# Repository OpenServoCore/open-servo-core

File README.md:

<p align="center">
  <picture>
    <source media="(prefers-color-scheme: dark)" srcset="docs/logo-dark.svg">
    
  </picture>
</p>

# OpenServoCore

> An open platform for turning cheap servos into smart actuators.

OpenServoCore (OSC) is open hardware and firmware that drops a CH32V006 control board into a $2-3 cloned hobby servo (SG90 and friends) and turns it into a Dynamixel-class smart actuator with position feedback, current sensing, bus addressing, and programmability. The bus speaks the **osc-native protocol**, a break-framed wire protocol designed to run whole on sub-$0.20 MCUs ([design writeup](https://aaronqian.com/log/2026-08-08-servo-protocol-stream-processing/)).

The thesis is the price point. At mass-production volume, an OSC swap board should add **no more than ~$1 to the BOM** of a cloned servo. That is cheap enough that upgrading every servo in a robot to smart becomes the default instead of a premium decision.

If you are here for a board, jump to [Boards](#boards). The firmware and its progress are in [Firmware](#firmware), and the design writeups are in [Reading](#reading).

## Status

**In active development. Nothing here is shippable yet.** What exists today:

- The **OSC Dev CH32** dev board is validated (Rev B) and you can order one.
- The firmware's protocol and bus transport are implemented and bench-proven on real silicon. Control loops are next.
- **[tinyboot](https://github.com/OpenServoCore/tinyboot)**, the OSC bootloader, has shipped v0.4.0 as its own repo.

The servo swap board (the one that goes inside a servo) is designed but not spun yet.

## Boards

**OSC Dev CH32** (`hardware/boards/osc-dev-v006/`) is the firmware development platform. It accepts any gutted hobby servo, takes power from USB-C, 1S-2S LiPo, or a WCH-LinkE, and fans out every rail and signal to edge test points. Rev B is validated. The [board README](hardware/boards/osc-dev-v006/README.md) has full schematics, pinouts, jumper behaviour, and bringup notes.

Want one? The full KiCad design files live in `hardware/boards/osc-dev-v006/`, ready to send to the board house of your choice.

There is also an experimental BLDC variant (`osc-dev-m007`) in the tree. It is unvalidated, so don't fab it.

## Firmware

The firmware is written in Rust and lives in `firmware/`. It is organized as chip-agnostic library crates (protocol, drivers, control table, discrete-event integration tests), a CH32 chip crate, and board binaries. The chip-agnostic layers compile and unit-test on a desktop with no hardware attached, and a discrete-event simulation runs the production crates ([the architecture writeup](https://aaronqian.com/log/2026-08-01-chip-agnostic-architecture-bare-metal-rust/) covers how).

What works today is the osc-native protocol and the servo bus transport. On the bench that means 0.5-3 Mbaud multi-servo status chains, ~30 µs ping turnaround at 1 Mbaud, and hardware CRC in both directions. The register-table conventions (flat control table, staged writes, alert semantics) will feel familiar if you have used Dynamixel. Control loops, persistence, and safety features are in progress, and build instructions will appear as the firmware matures.

Release and bench images are built with `scripts/build-image.sh <rev>` (add `--bench` for the bench-feature app, `--window` for the bench app with the window record). It exports the commit to one fixed directory (`$OSC_BUILD_ROOT`, default `~/.cache/osc-build`), builds every board image there and prints each image's sha1. The fixed path matters: cargo hashes the absolute path of each path dependency outside the workspace being built into crate metadata, rustc orders functions by the resulting symbol names, and so one commit built from two checkout paths links two layouts. On the V006 a layout shift moves timing by tens of cycles, so every image that is flashed, priced or compared comes from the script. [V006 performance](docs/v006-performance.md) covers the fetch model, the code-shape guards and how to measure a change.

The bootloader, [tinyboot](https://github.com/OpenServoCore/tinyboot), is a separate repo. It is part of the OSC firmware stack but versioned and released independently, and it supports more chips than the OSC boards on purpose (V003 / V00x / V103).

## Reading

The deep-dive writeups live on the blog:

- **[Stream processing on the wire](https://aaronqian.com/log/2026-08-08-servo-protocol-stream-processing/)**: the osc-native protocol design, and how the servo replies in tens of microseconds on a $0.16 chip.
- **[A chip-agnostic architecture for bare-metal embedded Rust](https://aaronqian.com/log/2026-08-01-chip-agnostic-architecture-bare-metal-rust/)**: the full firmware architecture, layer by layer, with code.
- **[Using the SPI peripheral as a DMA-fed CRC engine](https://aaronqian.com/log/2026-07-25-spi-as-dma-crc-engine/)**: hardware CRC on a chip with no CRC peripheral.
- **[HSI trim: calibrating a crystalless MCU over the bus](https://aaronqian.com/log/2026-07-18-hsi-trim-crystalless-mcu/)**: fleet clock calibration with nothing but the bus wire.
- **[Dynamixel 2.0 servo side: RX timing](https://aaronqian.com/log/2026-07-04-dynamixel-servo-side-rx-timing/)** and **[Fast Sync/Bulk Read](https://aaronqian.com/log/2026-07-11-dynamixel-servo-side-fast-sync-bulk-read/)**: the reference pair if you are building a Dynamixel-compatible device.

There is also one design doc in the repo worth reading. [Control theory](docs/control-theory.md) lays out the control design for the servo, with the cascaded loops, the estimators, and the sensing tiers. It is the plan, written ahead of the implementation, and it is not implemented yet.

## AI Use

I use AI heavily in this project. Claude (Fable 5, Opus 5, and earlier models) does a lot of the code generation and most of the document drafting, including parts of this README.

That does not make this vibe-coded. I review every line before it lands, and the result has to survive checks that don't care how the code was written. CI builds and tests every crate and cross-builds every board image. A discrete-event simulation runs the production crates and caught over a dozen real bugs before they reached silicon. The transport numbers above were measured on the bench. And this project was not built in one prompt. The history spans multiple years and many revisions of both the hardware and the firmware.

The documentation is more uneven than the code, and even this README could be easier to consume. That will improve, but working firmware comes first.

## Contributing

This is early. The most useful thing right now is **following along and asking questions** rather than opening PRs.

- **Discussions:** [github.com/OpenServoCore/open-servo-core/discussions](https://github.com/OpenServoCore/open-servo-core/discussions) is where design questions, ideas, and "is this on the roadmap?" go.
- **Build journey:** posts at [aaronqian.com](https://aaronqian.com) document the design decisions, dead ends, and what shipped each week.
- **Issues:** open ones are scoped to specific work. For now, contributor scope is small.

## License

OSC is fully open source.

- **Firmware**: [MIT](LICENSE-MIT) **OR** [Apache-2.0](LICENSE-APACHE), at your option (Rust ecosystem convention).
- **Hardware** (schematics, layouts, board files): [CERN-OHL-P v2.0](LICENSE-HARDWARE).

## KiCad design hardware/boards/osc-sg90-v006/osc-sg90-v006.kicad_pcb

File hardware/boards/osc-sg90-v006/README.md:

# OSC SG90 V006

> **Schematic and layout done, not fabricated yet.**
> The schematic now uses a standard SOT-23-5 LDO, a 1206 alloy shunt and JLCPCB basic 0402 passives. The layout file is on 4 layers with those footprints and nets in, at the old positions, and is not placed or rerouted yet: footprints overlap and the tracks are the earlier ones.
> Numbers and behavior below are design intent, not measured. The sense chain uses the dev board's (osc-dev-v006 Rev. 2B) topology with its own shunt and gain values, and firmware has never run on *this* board. Don't fab this without doing your own review first, and expect changes when bringup happens.

OpenServoCore swap board for SG90 and MG90 class hobby servos. It replaces the factory PCB inside the servo case. CH32V006 based, single-wire TTL servo bus ([osc-native protocol](../../../docs/osc-native-protocol.md)).

## Overview

- **MCU** - CH32V006F8U7 (RISC-V, 48 MHz, 62 KB flash, 8 KB RAM, UQFN-20, 105 C grade).
- **Motor driver** - TI DRV8837 (U3). H-bridge with IN1/IN2 PWM, 1.8 A peak, VM up to 11 V. The exposed pad sits on `PGND` with two vias into a small back-side pour.
- **Current sense** - 100 mOhm kelvin-connected low-side shunt (Rs1) feeding the MCU's on-chip op-amp in bare mode. An external four-resistor difference network sets G = 12000 / 1500 = 8. Rg1 / Rg2 (1K5) bring the shunt taps into the op-amp inputs, Rf2 (12K) is the feedback resistor, and Rf1 (12K) ties the + input to `VREF`, a 2K / 1K divider off `+3V3` (Rd1 / Rd2, about 1.09 V). Two pull-ups (Ri1 / Ri2, 4K7) lift the op-amp inputs to about 0.82 V. With the divider's source resistance and the pull-ups included, the chain works out to about 0.804 V/A (about 1 mA per count) with zero current at about 1.09 V, so both current directions are visible. The output saturates near +2.56 A and -1.32 A nominal. The network is 1 % parts, so the zero spreads about +/-0.2 V board to board and firmware has to measure it at boot.
- **LDO** - MaxLinear SPX3819M5-L-3-3 (U1), 500 mA, SOT-23-5, 2.5-16 V input (20 V absolute max), +/-1 % output, with thermal shutdown. `+3V3` is also the ADC reference, which is why the regulator is a 1 % part. EN is tied to `VSYS`, and Cp3 (10 nF) on the BYP pin lowers the output noise. Cp3 is optional, leave it out if space is short. The LDO runs straight off `VSYS`, so at 8.4 V each milliamp of `+3V3` costs about 5 mW in it, at 191 C/W junction to ambient. The `+3V3` budget is about 35 mA: the board itself draws about 14 mA, which leaves at least 15 mA for the J5 flex.
- **Servo bus** - single-wire half-duplex UART on `PC0`, wired straight to the MCU through a 22 Ohm series resistor (Rx1). No buffer. Dx1 (RClamp0521T) clamps the line at the connector, ahead of Rx1. Rx2 is a 100K idle keeper to `+3V3` on the MCU side, so `DATA` never floats with no host on the wire. It is too weak to be the bus pull-up, which lives at the host end.
- **Power input** - 2S Li-ion (up to 8.4 V) on the servo cable. There is no bulk capacitor, only about 10 uF of ceramic, so avoid hot-plugging into a stiff 2S supply until bringup has scoped it.
- **Debug** - WCH-LinkE over the CH32V006 1-wire SWDIO, on four pogo pads on the back (J3).
- **Position feedback** - potentiometer or analog magnetic encoder on J4 (one or two channels). The J5 flex landing also brings out two encoder inputs, but only for experiments (see J5).
- **Supply and terminal sense** - `VSYS` measured through its own divider, plus both motor terminals referenced to a common bias (`VB`) so back-EMF is readable while the bridge coasts.
- **Temperature** - onboard NTC (TH1, 10K, B25/50 3950) or an external NTC on J5, selected with JP2.
- **Board** - 13 x 10 mm, 4-layer 1.6 mm (JLCPCB JLC04161H-3313 stackup), ENIG. All parts on the front. The back only has wire pads, pogo pads and solder jumpers.

## MCU pinout

CH32V006F8U7, UQFN-20.

|Pin|Port|Net|Function used|
|---|---|---|---|
|1|PD7|`RST` (JP1 to `OPA_P`)|Op-amp + input (OPP1), once JP1 is closed|
|2|PA1|`VPOS1`|ADC A1, position channel 1|
|3|PA2|`VPOS2_NTC`|ADC A0, position channel 2 or NTC (JP2)|
|4|VSS|`GND`||
|5|PD0|`OPA_N`|Op-amp - input (OPN1)|
|6|VDD|`+3V3`||
|7|PC0|`DATA`|USART1 TX (Remap3), half-duplex bus|
|8|PC1|-|Not connected|
|9|PC2|-|Not connected|
|10|PC3|`DRV_EN`|DRV8837 nSLEEP, GPIO|
|11|PC4|`VSNS`|ADC A2, supply sense|
|12|PC5|`IN1`|TIM1 CH2 (Remap8), DRV8837 IN1|
|13|PC6|`IN2`|TIM1 CH3 (Remap8), DRV8837 IN2|
|14|PC7|-|Not connected|
|15|PD1|`SWDIO`|Debug|
|16|PD2|`ENCB`|ADC A3, encoder B|
|17|PD3|`ENCA`|ADC A4, encoder A|
|18|PD4|`OPA_OUT`|Op-amp output, ADC A7|
|19|PD5|`VSNA`|ADC A5, terminal A sense|
|20|PD6|`VSNB`|ADC A6, terminal B sense|
|EP|VSS|`GND`||

`IN1` / `IN2` sit on TIM1 CH2 / CH3 here, the reverse of the dev board. Firmware for this board has to swap `MOTOR_IN1_CH` and `MOTOR_IN2_CH` (in `firmware/servo-ch32/src/cfg/chip.rs`). There is no sg90 firmware config yet.

## Connectors

Everything is a solder pad. There are no through-hole parts.

### Servo cable - J1 (3 wire pads, front and back)

The front and back pads are tied together through via-in-pad, so a second servo can be chained off the back.

|Pin|Net|Notes|
|---|---|---|
|1|`GND`||
|2|`VSYS`|2S Li-ion, up to 8.4 V|
|3|`DATA`|Half-duplex UART, osc-native protocol|

### Motor - J2 (2 pads, back)

One pad at each left corner, where the SG90 motor tabs land.

|Pin|Net|
|---|---|
|1|`MOT_A`|
|2|`MOT_B`|

### Debug - J3 (4 pogo pads, 1.27 mm pitch, back)

|Pin|Net|
|---|---|
|1|`+3V3`|
|2|`GND`|
|3|`SWDIO`|
|4|`GND`|

### Position sensor - J4 (4 wire pads, 1.0 mm pitch, front)

|Pin|Net|Notes|
|---|---|---|
|1|`+3V3`|Pot top rail / sensor supply|
|2|`GND`||
|3|`POS1`|Wiper, or sensor channel 1|
|4|`POS2`|Sensor channel 2, only when JP2 is open|

Each channel goes through a 4K7 + 100 nF RC filter (fc about 340 Hz). Both filters match, so a sin/cos pair stays phase-matched.

### Flex - J5 (6 pads, back, left edge)

Landing for a flex that carries an external NTC, which works today. The two encoder inputs are experimental: there is no firmware for a motor-side encoder on this board, and the CH32V006 has no timers or CPU time left for one. A reflective IR pair at its benched 20 mA per LED draws about 40 mA, well past the `+3V3` budget at 8.4 V. For experiments, run the board from a lower supply (about 5 V or one cell), where the LDO drops much less.

|Pin|Net|Notes|
|---|---|---|
|1|`GND`||
|2|`+3V3`|Keep the load under about 15 mA, enough for two IR LEDs at about 4-5 mA each|
|3|`ENCA`||
|4|`ENCB`||
|5|`VNTC_EXT`|External NTC, needs its own pull-up on the flex|
|6|`GND`||

### Solder jumpers

- **JP1** - leave it open for the first flash, which writes `RST_MODE` so PD7 stops being the reset pin. Then close it. The op-amp + input shares PD7 with NRST.
- **JP2** - picks what ADC A0 reads. B-C is the onboard NTC, A-C is the external NTC on J5, and open leaves it on `POS2` from J4. It ships open.

## Design intent

These are the targets the board was laid out around. None are measured.

- **Ground split** - `PGND` (driver and motor current) and `GND` meet only at Rs1. The driver supply caps (Ch1-Ch3) return to `GND`, so the motor loop has to cross the shunt.
- **Current sense** - the shunt taps are kelvin net ties (NT1 / NT2) on the shunt pads, straight into the gain resistors. The front ground pour is kept off the op-amp network, with solid ground on In1 underneath.
- **Voltage sensing** - 10K / 2K2 dividers (ratio 0.180) on `VSNS`, `VSNA` and `VSNB`. 8.4 V reads 1.51 V at the ADC. The terminal divider bottoms return to `VB` (Rb1 1K / Rb2 220, about 0.60 V) instead of GND, so a terminal swinging below ground still reads.
- **Precision parts** - only two parts are picked with care. The shunt is a 1206 metal alloy part (JIERR JER1206F1R100, 1 %, 50 ppm, 1 W); if the 1206 does not fit, the backup is the 0805 Yageo PE0805FRF470R1L (C2935234, 1 %, 100 ppm, 0.5 W), and the LDO is the 1 % SPX3819 because it is the ADC reference. Every other resistor is a 1 % 100 ppm JLCPCB basic 0402 part. Firmware measures the current zero and `VB` at boot, and motor identification absorbs the fixed gain error of each board. The terminal filter caps are C0G.
- **Motor path** - the motor traces run on the back, 0.4 mm wide, with the In4 ground plane between them and the In2 signal layer.
- **Supply path** - `VSYS` runs from J1 to the driver as a pour on In3, next to the `+3V3` plane.

## Fabrication

- 4-layer JLCPCB stackup JLC04161H-3313, 1.6 mm, ENIG.
- 0.09 / 0.09 mm track and space, 0.3 / 0.45 mm vias.
- Via-in-pad is used under U2, U3 and on the connector pads. Order with epoxy filled and capped vias.
- Single-sided assembly. Every part is on the front.
- The design rules live in `osc-sg90-v006.kicad_dru`.

## Mechanical fit

Designed to drop into a standard SG90 / MG90 case:

- Motor tabs solder to J2.
- The pot or sensor wires solder to J4.
- The servo cable solders to J1.
- The debug pads stay reachable for bringup and reflashing.

Pad positions are still **to be confirmed against a physical case** when the first boards arrive.

## License

Hardware files (schematic, layout, board files in this directory) are licensed under [CERN-OHL-P v2.0](../../../LICENSE-HARDWARE). See the [top-level README](../../../README.md#license) for the full licensing picture.

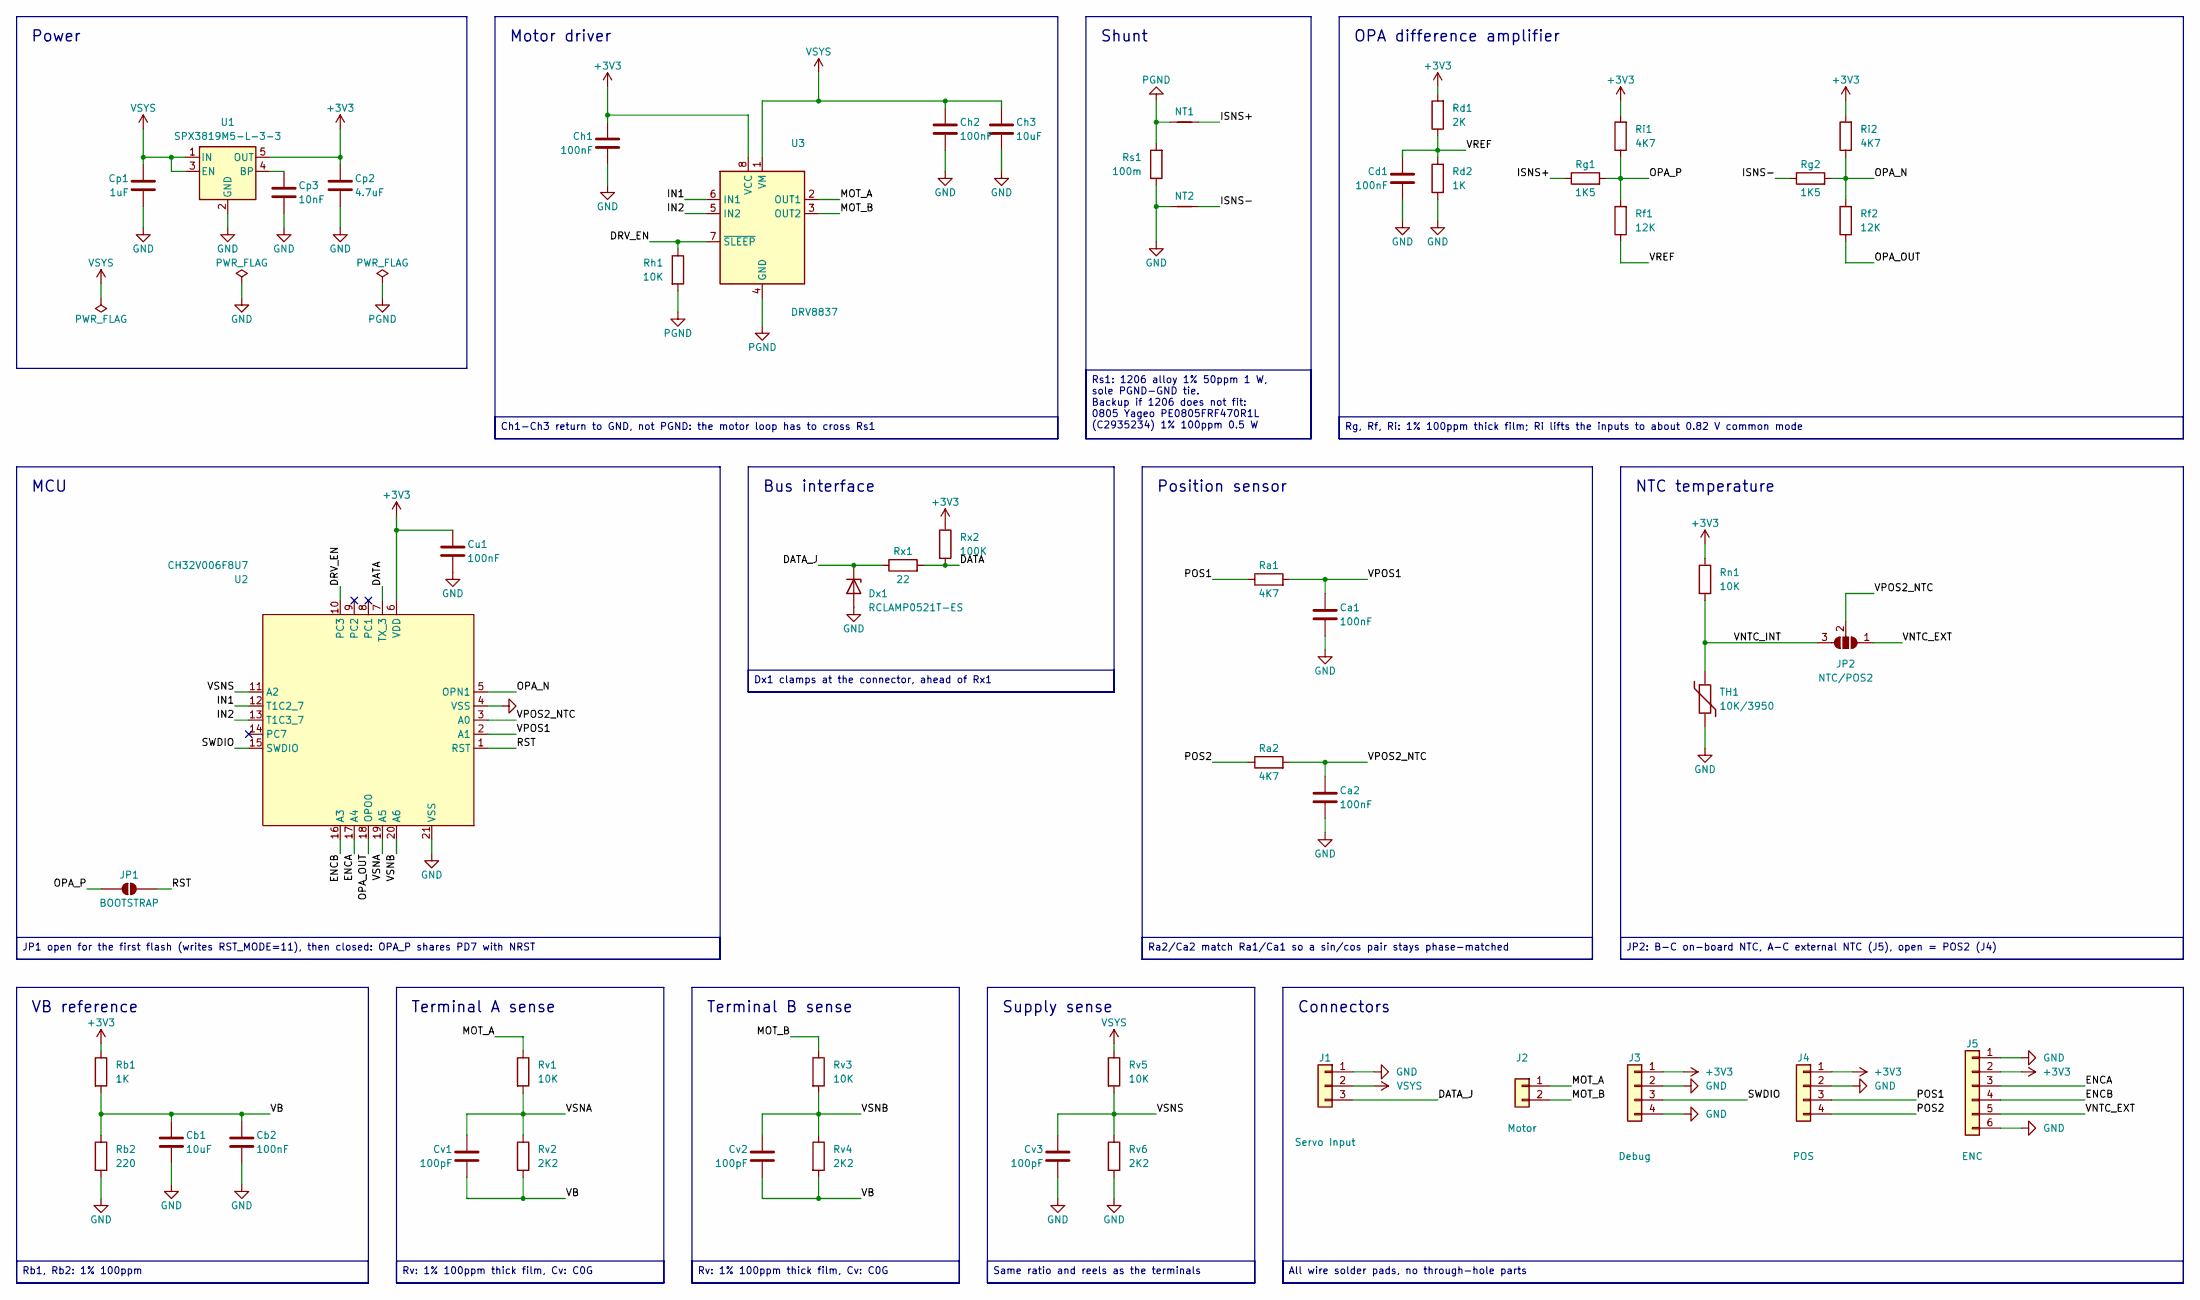
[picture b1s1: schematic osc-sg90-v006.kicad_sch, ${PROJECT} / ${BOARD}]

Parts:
Ca1, Ca2: 100nF; C_0402_1005Metric; LCSC C307331
Cb1: 10uF; C_0402_1005Metric; LCSC C15525
Cb2: 100nF; C_0402_1005Metric; LCSC C307331
Cd1: 100nF; C_0402_1005Metric; LCSC C307331
Ch1, Ch2: 100nF; C_0402_1005Metric; LCSC C307331
Ch3: 10uF; C_0603_1608Metric; LCSC C96446
Cp1: 1uF; C_0402_1005Metric; LCSC C52923
Cp2: 4.7uF; C_0402_1005Metric; LCSC C23733
Cp3: 10nF; C_0402_1005Metric; LCSC C15195
Cu1: 100nF; C_0402_1005Metric; LCSC C307331
Cv1, Cv2, Cv3: 100pF; C_0402_1005Metric; LCSC C1546
Dx1: RCLAMP0521T-ES; D_SOD-882_Tight; LCSC C5180263
J1: Servo Input; Wire_Pads_1x03_P1.5mm_DualSide
J2: Motor; Wire_Pads_1x02_P8.1mm
J3: Debug; Debug_Pads_1x4_P1.27mm
J4: POS; Wire_Pads_1x04_P1.0mm
J5: ENC; Flex_Landing_1x06_P1.0mm
JP1: BOOTSTRAP; SolderJumper-2_P0.58mm_Open_TrianglePad0.4x0.6mm
JP2: NTC/POS2; SolderJumper-3_P0.8mm_Open_TrianglePad0.4x0.6mm
NT1, NT2: NetTie_2; NetTie-2_SMD_0.127mm
Ra1, Ra2: 4K7; R_0402_1005Metric; LCSC C25900
Rb1: 1K; R_0402_1005Metric; LCSC C11702
Rb2: 220; R_0402_1005Metric; LCSC C25091
Rd1: 2K; R_0402_1005Metric; LCSC C4109
Rd2: 1K; R_0402_1005Metric; LCSC C11702
Rf1, Rf2: 12K; R_0402_1005Metric; LCSC C25752
Rg1, Rg2: 1K5; R_0402_1005Metric; LCSC C25867
Rh1: 10K; R_0402_1005Metric; LCSC C25744
Ri1, Ri2: 4K7; R_0402_1005Metric; LCSC C25900
Rn1: 10K; R_0402_1005Metric; LCSC C25744
Rs1: 100m; R_1206_3216Metric; LCSC C49164948
Rv1, Rv3, Rv5: 10K; R_0402_1005Metric; LCSC C25744
Rv2, Rv4, Rv6: 2K2; R_0402_1005Metric; LCSC C25879
Rx1: 22; R_0402_1005Metric; LCSC C25092
Rx2: 100K; R_0402_1005Metric; LCSC C25741
TH1: 10K/3950; R_0402_1005Metric; LCSC C49247682
U1: SPX3819M5-L-3-3; SOT-23-5; LCSC C9055
U2: CH32V006F8U7; UQFN-20_L3.0-W3.0-P0.40-BL-EP1.7; LCSC C55112440
U3: DRV8837; Texas_DSG0008A_WSON-8-1EP_2x2mm_P0.5mm_EP0.9x1.6mm_Tight; LCSC C39159

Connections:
+3V3: Ch1.1, Cp2.1, Cu1.1, J3.1, J4.1, J5.2, Rb1.1, Rd1.2, Ri1.2, Ri2.2, Rn1.1, Rx2.1, U1.5 (OUT), U2.6 (VDD), U3.8 (VCC)
/DATA: Rx1.2, Rx2.2, U2.7 (TX_3)
/DATA_J: Dx1.1 (K), J1.3, Rx1.1
/DRV_EN: Rh1.1, U2.10 (PC3), U3.7 (~SLEEP)
/ENCA: J5.3, U2.17 (A4)
/ENCB: J5.4, U2.16 (A3)
/IN1: U2.12 (T1C2_7), U3.6 (IN1)
/IN2: U2.13 (T1C3_7), U3.5 (IN2)
/ISNS+: NT1.1, Rg1.1
/ISNS-: NT2.1, Rg2.1
/MOT_A: J2.1, Rv1.1, U3.2 (OUT1)
/MOT_B: J2.2, Rv3.1, U3.3 (OUT2)
/OPA_N: Rf2.2, Rg2.2, Ri2.1, U2.5 (OPN1)
/OPA_OUT: Rf2.1, U2.18 (OPO0)
/OPA_P: JP1.1 (A), Rf1.2, Rg1.2, Ri1.1
/POS1: J4.3, Ra1.1
/POS2: J4.4, Ra2.1
/RST: JP1.2 (B), U2.1 (RST)
/SWDIO: J3.3, U2.15 (SWDIO)
/VB: Cb1.1, Cb2.1, Cv1.2, Cv2.2, Rb1.2, Rb2.1, Rv2.2, Rv4.2
/VNTC_EXT: J5.5, JP2.1 (A)
/VNTC_INT: JP2.3 (B), Rn1.2, TH1.1
/VPOS1: Ca1.1, Ra1.2, U2.2 (A1)
/VPOS2_NTC: Ca2.1, JP2.2 (C), Ra2.2, U2.3 (A0)
/VREF: Cd1.1, Rd1.1, Rd2.2, Rf1.1
/VSNA: Cv1.1, Rv1.2, Rv2.1, U2.19 (A5)
/VSNB: Cv2.1, Rv3.2, Rv4.1, U2.20 (A6)
/VSNS: Cv3.1, Rv5.2, Rv6.1, U2.11 (A2)
GND: Ca1.2, Ca2.2, Cb1.2, Cb2.2, Cd1.2, Ch1.2, Ch2.2, Ch3.2, Cp1.2, Cp2.2, Cp3.2, Cu1.2, Cv3.2, Dx1.2 (A), J1.1, J3.2, J3.4, J4.2, J5.1, J5.6, NT2.2, Rb2.2, Rd2.1, Rs1.1, Rv6.2, TH1.2, U1.2 (GND), U2.4 (VSS), U2.21 (VSS)
unnamed: Cp3.1, U1.4 (BP)
PGND: NT1.2, Rh1.2, Rs1.2, U3.4 (GND), U3.9 (GND)
VSYS: Ch2.1, Ch3.1, Cp1.1, J1.2, Rv5.1, U1.1 (IN), U1.3 (EN), U3.1 (VM)

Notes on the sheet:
Bus interface
NTC temperature
Connectors
OPA difference amplifier
VB reference
Shunt
Terminal A sense
Supply sense
MCU
Motor driver
Power
Position sensor
Terminal B sense
Same ratio and reels as the terminals
Rb1, Rb2: 1% 100ppm
All wire solder pads, no through-hole parts
Rs1: 1206 alloy 1% 50ppm 1 W, sole PGND-GND tie. Backup if 1206 does not fit: 0805 Yageo PE0805FRF470R1L (C2935234) 1% 100ppm 0.5 W
Rg, Rf, Ri: 1% 100ppm thick film; Ri lifts the inputs to about 0.82 V common mode
Rv: 1% 100ppm thick film, Cv: C0G
Ch1-Ch3 return to GND, not PGND: the motor loop has to cross Rs1
Dx1 clamps at the connector, ahead of Rx1
JP2: B-C on-board NTC, A-C external NTC (J5), open = POS2 (J4)
JP1 open for the first flash (writes RST_MODE=11), then closed: OPA_P shares PD7 with NRST
Ra2/Ca2 match Ra1/Ca1 so a sin/cos pair stays phase-matched

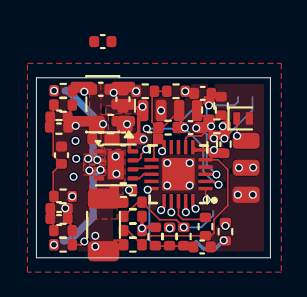
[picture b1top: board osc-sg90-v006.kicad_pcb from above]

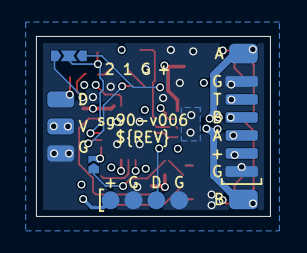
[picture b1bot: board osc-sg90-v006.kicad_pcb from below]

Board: 4 copper layers, 13.0 x 10.0 mm, 52 parts (5 on the bottom side), 32 nets.

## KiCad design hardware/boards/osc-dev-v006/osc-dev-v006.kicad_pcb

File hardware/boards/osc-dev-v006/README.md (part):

# OSC Dev V006 - Rev. 2B

> **Rev. 2B: schematic and layout done, not fabricated yet.**
> Its sense chain is what the reworked Rev. 2A boards already run. Rev. 2A board #1 runs an MG90 on 2S. Position calibration, the position table, motor identification and closed-loop verify all pass on it, and the sense chain is graded in [Measured on board #1](#measured-on-board-1).
> Not exercised yet: the encoder inputs (J6 / J11), Qwiic, and the second position channel. See [Still open](#still-open).
> **Fabricate this at your own risk!**

See [CHANGELOG.md](CHANGELOG.md) for revision history.

This is the OpenServoCore firmware development and validation board. It is built around the CH32V006F8P6 and designed to accept any gutted hobby servo (SG90, MG90, and similar), so firmware can be brought up and characterized against real motor / pot / encoder hardware.

KiCad render of Rev. 2A, not yet updated for Rev. 2B.

## Overview

- **MCU** - CH32V006F8P6 (RISC-V, 48 MHz, 62 KB flash, 8 KB RAM, TSSOP20). Every pin is used, including the reset pin.
- **Motor driver** - TI DRV8212PDSGR (U3). H-bridge with IN1/IN2 PWM. 4 A peak, VM 1.65-11 V. Continuous current is thermally limited on this layout to about 1.4 A at room temperature; the exposed pad sits on the top-only `PGND` island and dumps heat through the prepreg into the ground plane, not into a copper plane of its own.
- **Current sense** - 60 mOhm kelvin-connected low-side shunt (Rs1) feeding the MCU's on-chip op-amp in bare mode. An external four-resistor difference network sets G = 14.88 against a 1.09 V bias, so both current directions are visible. Two pull-ups lift the op-amp inputs to about 0.75 V.
- **LDO** - HT7533-1 (U1) for the 3.3 V logic rail. No thermal shutdown, and its 500 mW budget at 2S caps the `+3V3` load at about 55 mA, board included, so keep add-ons on the 3V3 pins light and mind probe slips on the 3V3 headers. The DRV8212P VCC sits on the same `+3V3` as the MCU.
- **Servo bus** - single-wire half-duplex UART on `PC0`, wired straight to the MCU through a 22 Ohm series resistor. No buffer, no TX_EN. Direction turnaround and RX timing are firmware's job.
- **Telemetry** - no dedicated pin. Telemetry rides the `DATA` wire as bounded CRC'd bursts, so there is no second UART on the board.
- **Qwiic** - SH 1.0 mm 4P I2C connector (J3) for an encoder module, either magnetic (I2C) or a quadrature encoder breakout.
- **Power input** - 1S-2S LiPo (3.0-8.4 V) via JST-PH, or the WCH-LinkE 5 V rail. Either or both, OR'd through SS54 Schottkys (about 0.25 V drop).
- **Debug** - WCH-LinkE over the CH32V006 1-wire SWDIO, on a 1x03 header (J2).
- **Position feedback** - potentiometer or analog magnetic encoder on J5, I2C encoder on J3, or an ADC-sampled IR encoder on J6 (pins) or J11 (flex landing).
- **Supply and terminal sense** - `VSYS` measured directly through its own divider, plus both motor terminals referenced to a common bias so back-EMF is readable while the bridge coasts.
- **Temperature** - onboard NTC (TH1) or external NTC (J7), selected with JP2.
- **Board** - 50 x 40 mm, 6-layer 1.6 mm (JLCPCB JLC06161H-3313 stackup), ENIG, via-in-pad.

### Changed from Rev. 2A

Rev. 2B puts the bench rework of the Rev. 2A boards into copper. See [CHANGELOG.md](CHANGELOG.md) for the full list.

- Op-amp input pull-ups (Ri1 / Ri2) lift the input common mode to about 0.75 V.
- `VREF` moves to 1.09 V with a single Rd2.
- No DNP footprints left. The comp caps, input and output caps, kelvin filter, kelvin 0R swap points and the driver VCC 0R are gone.
- Low-capacitance bus ESD clamp, 22 Ohm `DATA` series resistor and a 100K idle keeper.
- LED resistors picked so the lamps look about as bright as each other.
- Via-in-pad drills of 0.4 mm max, so JLCPCB fills every one.

### Changed from Rev. B

Rev. 2A was a big respin. Here is what changed:

- The 74LVC2G241 UART buffer is deleted. The bus `DATA` line connects straight to the MCU through a 33 Ohm series resistor (Rx1), and RX timing moved fully into firmware.
- Current sense is reworked around the CH32V006's on-chip op-amp: kelvin shunt, external difference network, and a VREF bias for bidirectional current.
- Motor terminal sense divider bottoms return to a bias node (`VB`) instead of GND, so both terminals stay readable during coast.
- `VSNS` is back, on its own pin, as a direct divider off `VSYS`.
- USB-C and screw-terminal power inputs are dropped. Battery and LinkE 5 V remain.
- The PWM servo header is dropped. Qwiic (I2C) is added.
- The edge test-point hook rails are replaced by nine 1.0 mm probe pads, most of them in two rows next to the sense network. See [Test points](#test-points--probing).
- 4 layers to 6 layers, and all connectors are renumbered.

## MCU pinout

CH32V006F8P6, TSSOP20. The "Function used" column is what the board wires the pin for.

|Pin|Port|Net|Function used|
|---|---|---|---|
|1|`PD4`|`OPA_OUT`|Op-amp output (`OPO0`). The same pin is ADC `A7`, which samples it.|
|2|`PD5`|`VSNA`|ADC `A5`, motor terminal A sense.|
|3|`PD6`|`VSNB`|ADC `A6`, motor terminal B sense.|
|4|`PD7`|`RST`|`nRST` from the factory. After the option byte flip it becomes the op-amp `+` input (`OPP1`) through JP1. See [First boot](#first-boot).|
|5|`PA1`|`VPOS1`|ADC `A1`, position channel 1: pot wiper or the first transducer output (RC-filtered).|
|6|`PA2`|`VPOS2_NTC`|ADC `A0`, position channel 2 for a dual-transducer sensor, or the NTC divider when JP2 is jumped.|
|7|-|`GND`|`VSS`.|
|8|`PD0`|`OPA_N`|Op-amp `-` input (`OPN1`), difference network summing node.|
|9|-|`+3V3`|`VDD`.|
|10|`PC0`|`DATA`|USART1 TX (remap 3), half-duplex (HDSEL) servo bus. Also TIM2 CH1 (remap 4) as the input of the bus break wake.|
|11|`PC1`|`SDA`|I2C1 SDA, Qwiic (J3).|
|12|`PC2`|`SCL`|I2C1 SCL, Qwiic (J3).|
|13|`PC3`|`DRV_EN`|GPIO to the DRV8212P nSLEEP. A 10K pulldown (Rh1) keeps the driver asleep at reset.|
|14|`PC4`|`VSNS`|ADC `A2`, `VSYS` supply divider.|
|15|`PC5`|`DRV_IN2`|TIM1 CH2 (remap 8), H-bridge PWM.|
|16|`PC6`|`DRV_IN1`|TIM1 CH3 (remap 8), H-bridge PWM.|
|17|`PC7`|`STAT`|STAT LED, active low, driven as a plain GPIO. The only firmware-driven lamp.|
|18|`PD1`|`SWDIO`|1-wire debug, 100 Ohm series (Ru1) to J2.|
|19|`PD2`|`ENCB`|Encoder B. ADC `A3`, analog quadrature sampling.|
|20|`PD3`|`ENCA`|Encoder A. ADC `A4`, analog quadrature sampling.|

TIM1 runs center-aligned PWM on IN1/IN2 at 20 kHz, and its update event triggers the ADC scans at the counter crest and trough (see [PWM and ADC timing](#pwm-and-adc-timing)). Remap 8 puts TIM1 CH4 on `PC7`, but CH4's output stays off (its compare starts the ADC's injected group) and STAT is a GPIO.

## Connectors

All 2.54 mm pin headers are vertical through-hole.

### Battery - J1

JST-PH 2P horizontal. **1S-2S LiPo only (3.0-8.4 V).** The DRV8212P caps the safe motor rail at 11 V, so 3S is not supported. This input is OR'd into `VSYS` through an SS54 (Dp1), so it coexists with LinkE power.

### WCH-LinkE - J2

1x03 pin header (2.54 mm) for the WCH-LinkE programmer / debugger.

|Pin|Net|Notes|
|---|---|---|
|1|`VPROG`|LinkE 5 V rail, OR'd into `VSYS` through an SS54 (Dp2).|
|2|`GND`||
|3|`SWDIO`|1-wire debug, through a 100 Ohm series resistor (Ru1).|

Three pins is the whole header now. Telemetry rides the servo bus, so the LinkE's TX / RX are not connected to anything.

Plugging in the LinkE alone is enough to power the board. Very handy for firmware-only sessions.

### Qwiic - J3

SH 1.0 mm 4P (GND / +3V3 / SDA / SCL), standard [Qwiic](https://www.sparkfun.com/qwiic) pinout. 4K7 pull-ups (Rq1 / Rq2) sit on the MCU side, and 100 Ohm series resistors (Rq3 / Rq4) sit between the MCU and the connector.

This one is meant for an encoder module rather than generic sensors: an I2C magnetic encoder (MT6701 / AS5600 breakout) or a quadrature encoder adapter. The board has no hardware quadrature counting (see J6), so Qwiic is the flexible stand-in for it. I2C1 is polled.

### Motor - J4

1x02 pin header carrying `MOT_A` / `MOT_B` straight off the DRV8212P outputs. Through-hole, so the high-current path stays zero-via.

### Position - J5

1x04 pin header, `+3V3` / `GND` / `POS1` / `POS2`. It takes:

- The gutted servo's **potentiometer** on `POS1`. Excitation comes from `+3V3` and the wiper goes into `POS1`. Excitation and ADC reference share the same rail, so the reading is ratiometric and supply drift cancels out.
- An **analog-output magnetic encoder** (e.g. MT6701 in ratiometric analog mode) as a drop-in pot replacement on the same first three pins.
- A **dual-output transducer** (sin / cos style, the tier-2 sensor) on `POS1` and `POS2`. `POS2` shares its ADC pin with the NTC, so leave JP2 open in this mode; the on-board temperature reading is given up for the second channel. Both channels sit behind identical 4K7 / 100nF filters (Ra1 / Ca1 and Ra2 / Ca2) so the pair stays phase-matched.

With a pot or a single-output encoder, leave `POS2` unconnected and jump JP2 for the NTC. For a digital magnetic encoder use Qwiic (I2C) instead.

### Encoder - J6

2x02 pin header. `+3V3` / `GND` on one row, `ENCA` / `ENCB` on the other, going into ADC channels `A4` / `A3`. Silk reads `QA` / `QB` for the two phases.

This is a future expansion connector for an ADC-sampled custom IR quadrature encoder, in the style of [ServoProject](https://github.com/adamb314/ServoProject). The analog A/B phases get oversampled and interpolated for sub-count resolution. Hardware quadrature counting is not possible here since `PD2` / `PD3` don't carry TIM2 CH1/CH2, so I never considered it. A digital encoder belongs on Qwiic instead.

### Motor encoder flex - J11

Six bare pads at 1.0 mm pitch for the motor-shaft encoder flex, attached tin-and-iron: the flex fingers are pre-tinned, laid on the pads and pressed with an iron, then hot glue over the pad row takes the strain. The footprint pair (`Flex_Landing_1x06_P1.0mm` on the board, `Flex_Fingers_1x06_P1.0mm` on the flex) lives in the shared library, and the same landing goes on the swap board, so the dev board rehearses the real attach. Pin 1 is at the bracket mark.

|Pin|Net|Notes|
|---|---|---|
|1|`GND`|Outer ground, guards the pair.|
|2|`+3V3`|Emitter and phototransistor supply.|
|3|`ENCA`|IR sensor A, ADC `A4`. Same net as J6. Silk `QA`.|
|4|`ENCB`|IR sensor B, ADC `A3`. Same net as J6. Silk `QB`.|
|5|`VNTC_EXT`|Thermistor on the motor can, into the external leg of JP2. The divider resistor sits on the flex. Silk `NTC`.|
|6|`GND`|Outer ground.|

J6 and J11 are the same encoder input in two shapes: pins for a wired breakout or the bench coupon, the landing for the flex. Populate one.

### External NTC - J7

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
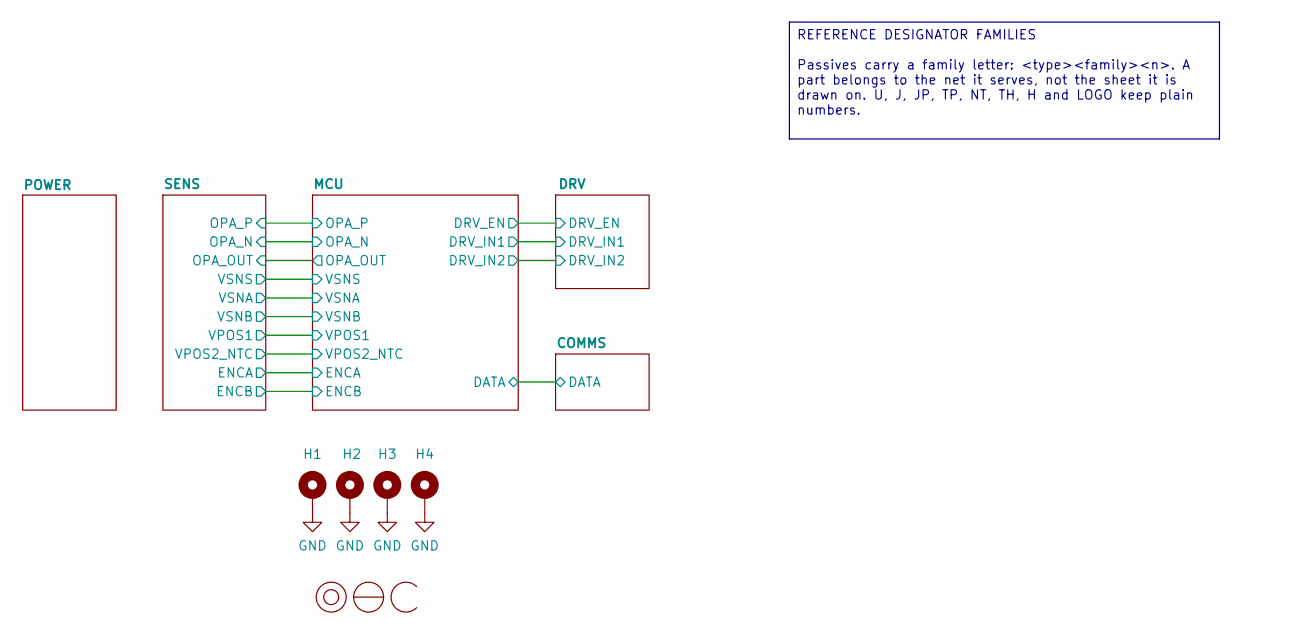
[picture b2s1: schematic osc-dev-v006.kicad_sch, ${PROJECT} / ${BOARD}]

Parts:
H1, H2, H3, H4: MountingHole_Pad_MP; MountingHole_2.2mm_M2_ISO7380_Pad
LOGO1: osc-logo; osc

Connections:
GND: H1.1 (1_1), H2.1 (1_1), H3.1 (1_1), H4.1 (1_1); also elsewhere on the board

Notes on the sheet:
REFERENCE DESIGNATOR FAMILIES Passives carry a family letter: <type><family><n>. A part belongs to the net it serves, not the sheet it is drawn on. U, J, JP, TP, NT, TH, H and LOGO keep plain numbers.

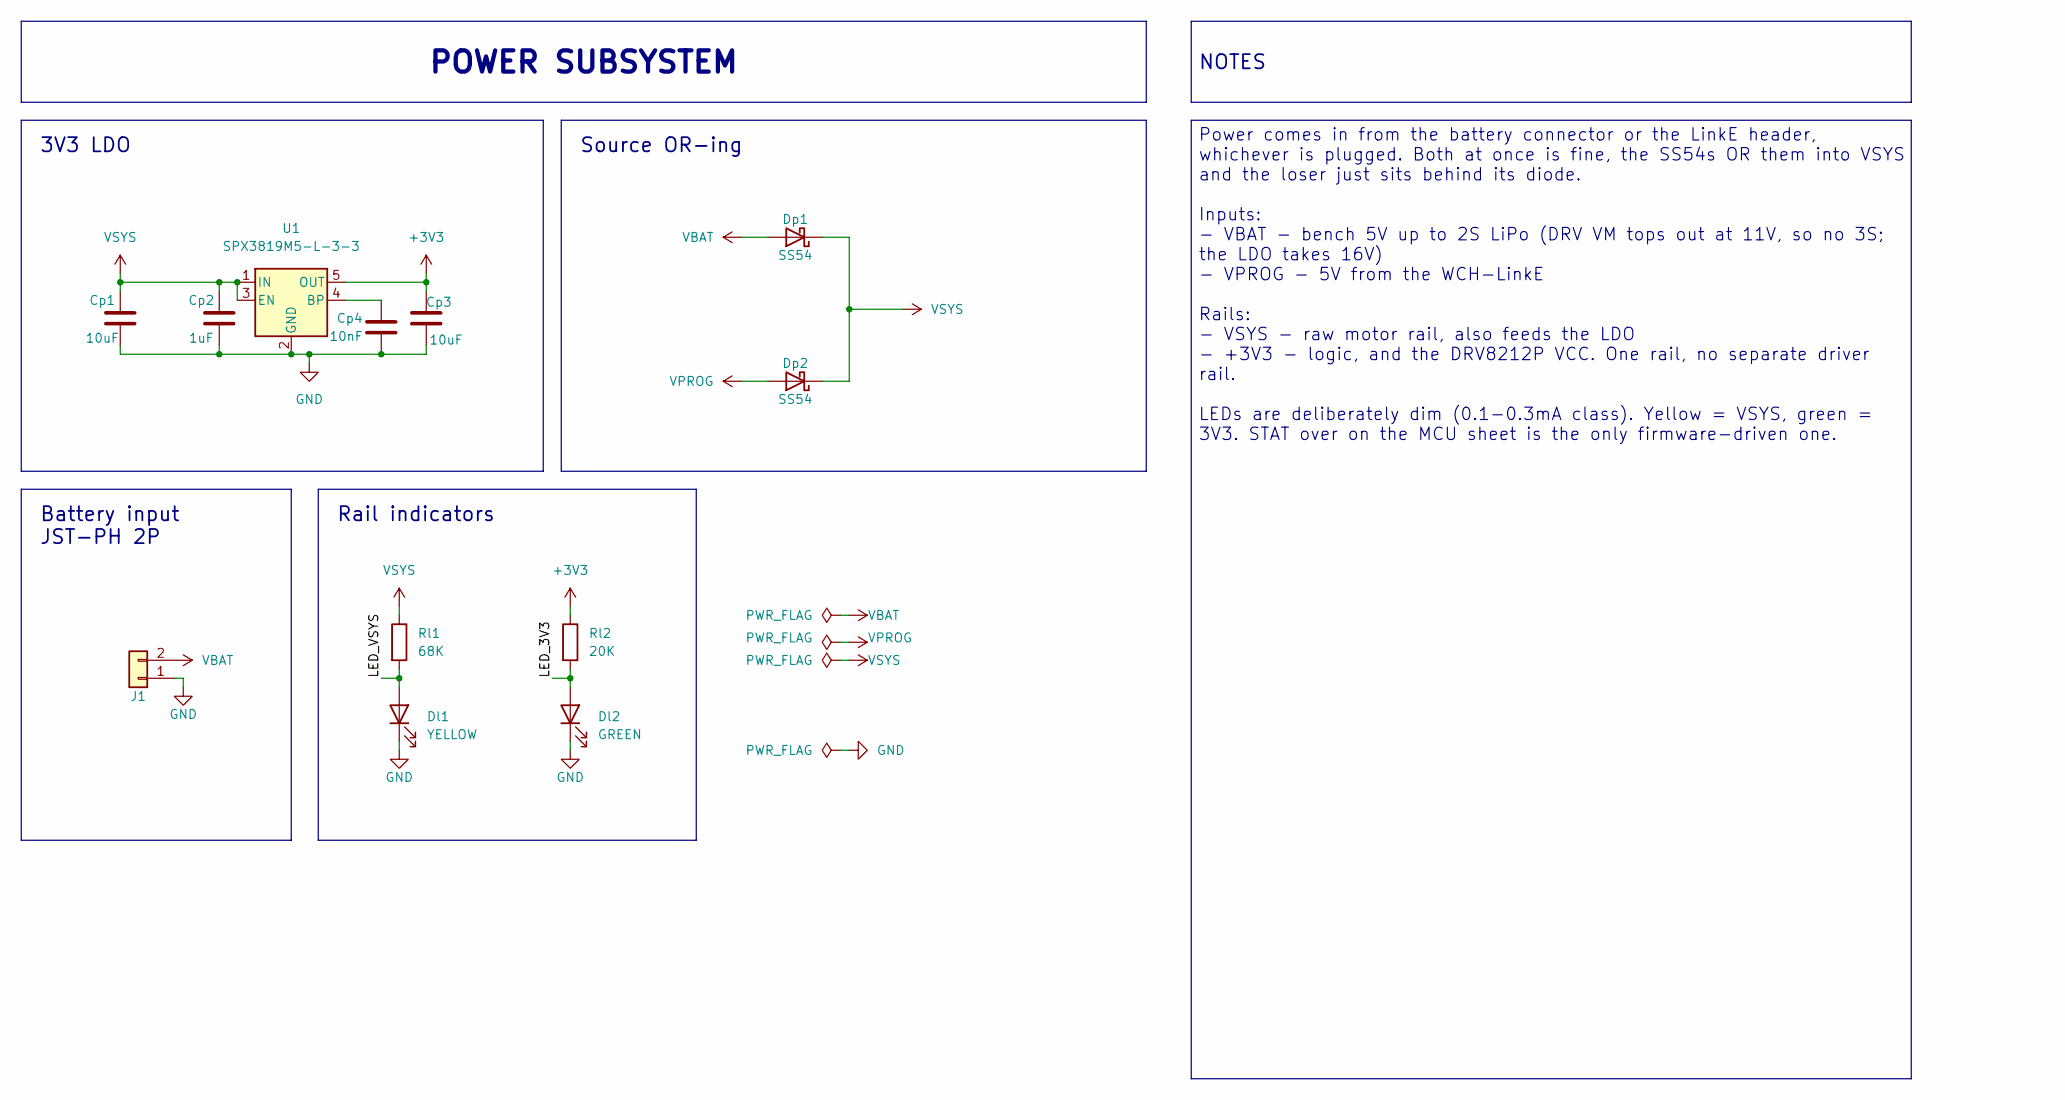
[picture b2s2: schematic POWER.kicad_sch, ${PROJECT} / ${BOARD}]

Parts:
Cp1, Cp3: 10uF; C_0805_2012Metric_Pad1.18x1.45mm_HandSolder; LCSC C15850
Cp2: 1uF; C_0603_1608Metric_Pad1.08x0.95mm_HandSolder; LCSC C559769
Cp4: 10nF; C_0603_1608Metric_Pad1.08x0.95mm_HandSolder; LCSC C57112
Dl1: YELLOW; LED_0603_1608Metric_Pad1.05x0.95mm_HandSolder; LCSC C497929
Dl2: GREEN; LED_0603_1608Metric_Pad1.05x0.95mm_HandSolder; LCSC C497927
Dp1, Dp2: SS54; D_SMA_Handsoldering; LCSC C22452
J1: JST-PH-H; CONN-TH_S2B-PH-K-S-LF-SN; LCSC C173752
Rl1: 68K; R_0603_1608Metric_Pad0.98x0.95mm_HandSolder; LCSC C2907063
Rl2: 20K; R_0603_1608Metric_Pad0.98x0.95mm_HandSolder; LCSC C2907011
U1: SPX3819M5-L-3-3; SOT-23-5_HandSoldering; LCSC C9055

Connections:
+3V3: Cp3.1, Rl2.1, U1.5 (OUT); also elsewhere on the board
/POWER/LED_3V3: Dl2.2 (A), Rl2.2
/POWER/LED_VSYS: Dl1.2 (A), Rl1.2
GND: Cp1.2, Cp2.2, Cp3.2, Cp4.2, Dl1.1 (K), Dl2.1 (K), J1.1, U1.2 (GND); also elsewhere on the board
unnamed: Cp4.1, U1.4 (BP)
VBAT: Dp1.2 (A), J1.2
VPROG: Dp2.2 (A); also elsewhere on the board
VSYS: Cp1.1, Cp2.1, Dp1.1 (K), Dp2.1 (K), Rl1.1, U1.1 (IN), U1.3 (EN); also elsewhere on the board

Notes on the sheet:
Battery input JST-PH 2P
3V3 LDO
Rail indicators
Source OR-ing
NOTES
Power comes in from the battery connector or the LinkE header, whichever is plugged. Both at once is fine, the SS54s OR them into VSYS and the loser just sits behind its diode. Inputs: - VBAT - bench 5V up to 2S LiPo (DRV VM tops out at 11V, so no 3S; the LDO takes 16V) - VPROG - 5V from the WCH-Li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
POWER SUBSYSTEM

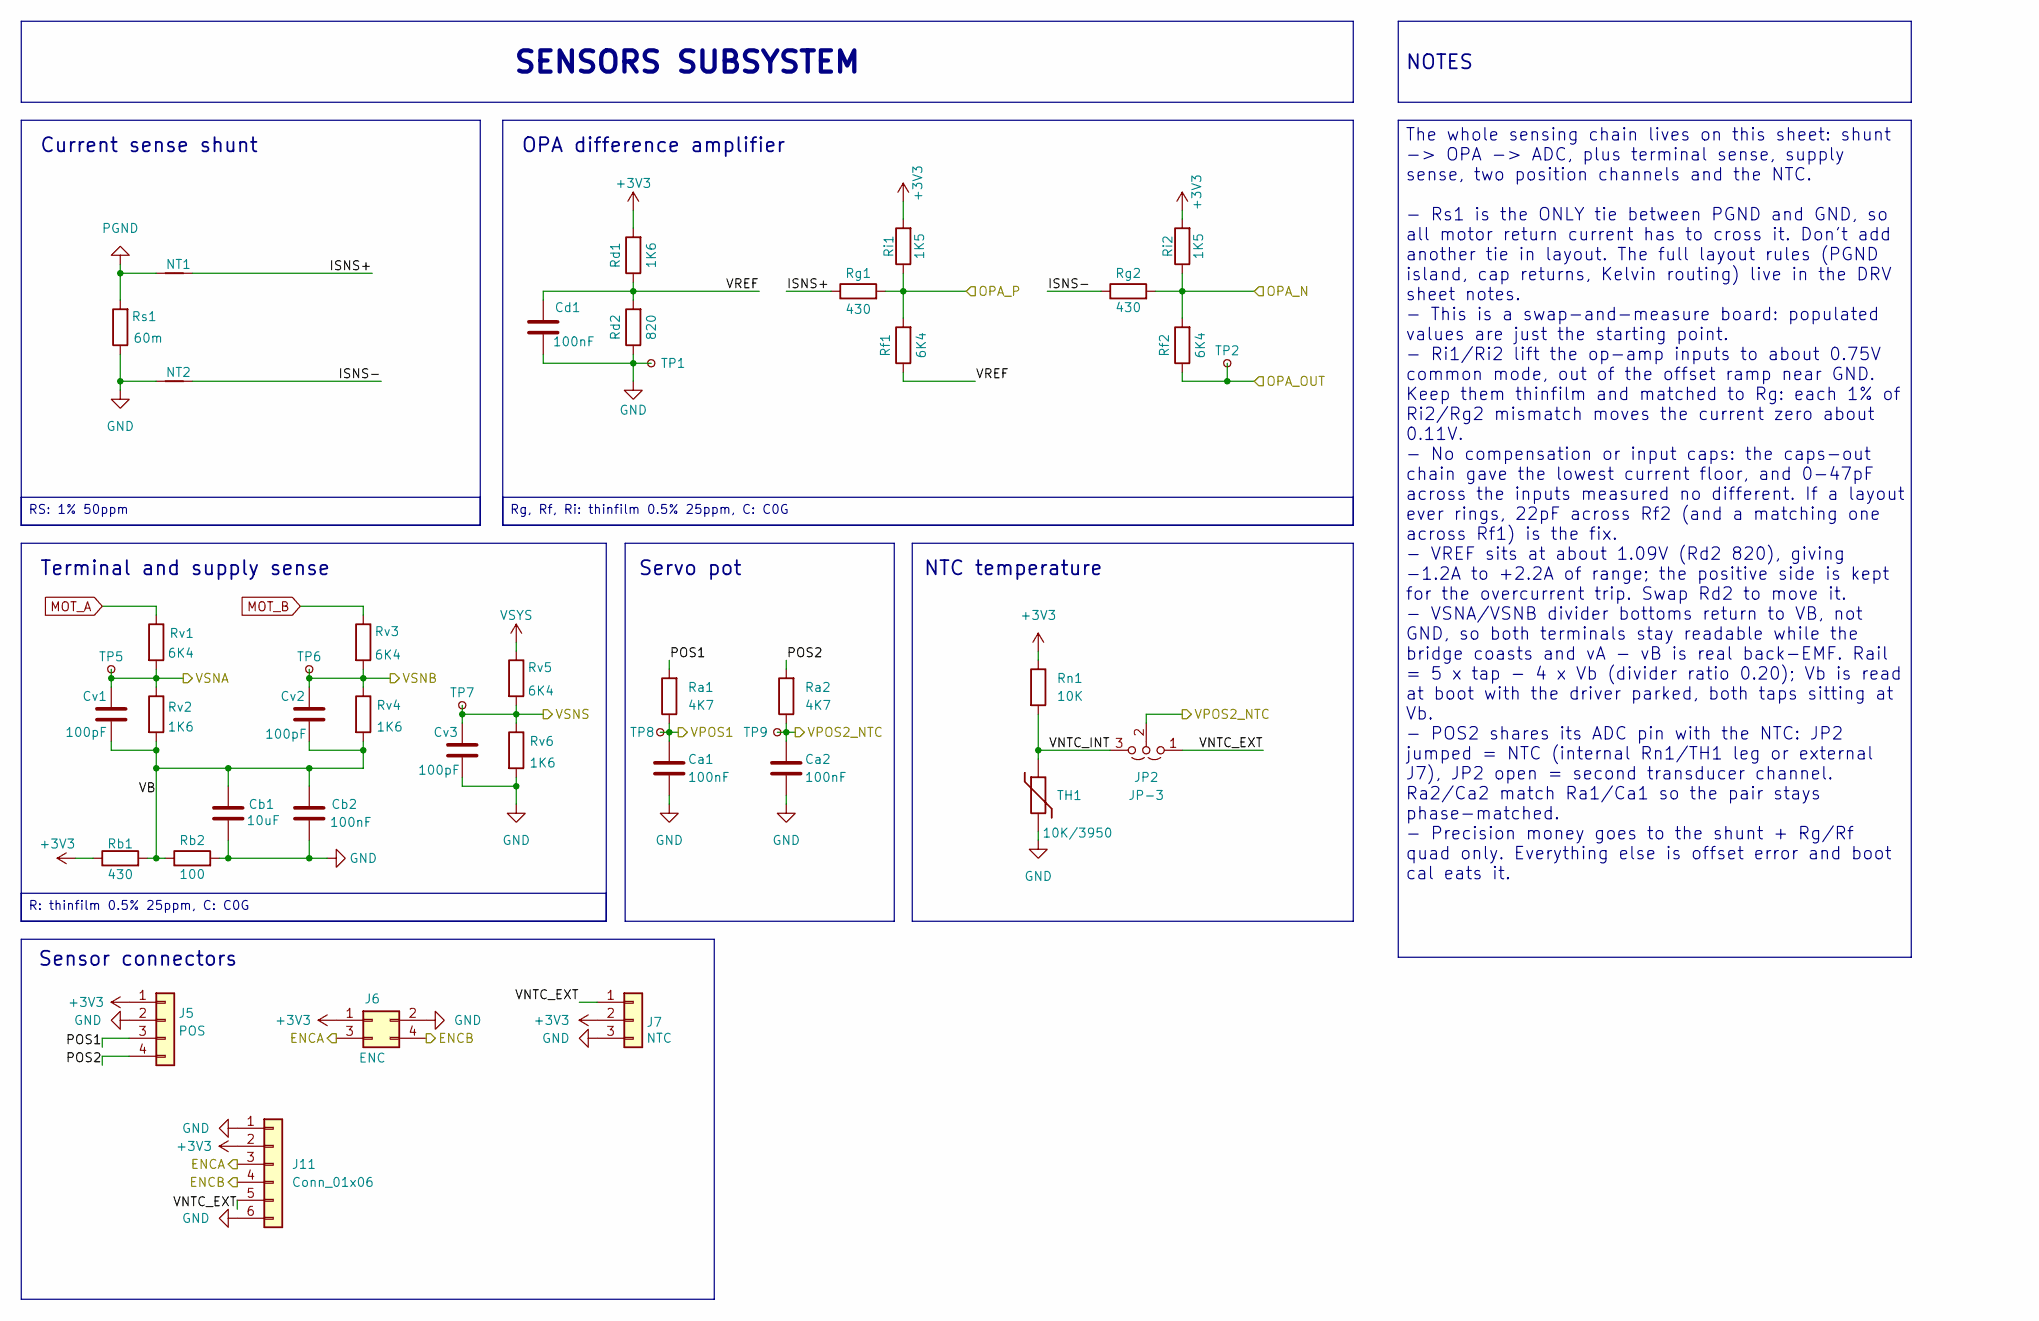
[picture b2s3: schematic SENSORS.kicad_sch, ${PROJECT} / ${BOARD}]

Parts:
Ca1, Ca2: 100nF; C_0603_1608Metric_Pad1.08x0.95mm_HandSolder; LCSC C14663
Cb1: 10uF; C_0805_2012Metric_Pad1.18x1.45mm_HandSolder; LCSC C15850
Cb2: 100nF; C_0603_1608Metric_Pad1.08x0.95mm_HandSolder; LCSC C14663
Cd1: 100nF; C_0603_1608Metric_Pad1.08x0.95mm_HandSolder; LCSC C14663
Cv1, Cv2, Cv3: 100pF; C_0603_1608Metric_Pad1.08x0.95mm_HandSolder; LCSC C14665
J5: POS; PinHeader_1x04_P2.54mm_Vertical
J6: ENC; PinHeader_2x02_P2.54mm_Vertical; LCSC C66690
J7: NTC; PinHeader_1x03_P2.54mm_Vertical; LCSC C49257
J11: Conn_01x06; Flex_Landing_1x06_P1.0mm
JP2: JP-3; PinHeader_1x03_P2.54mm_Vertical; LCSC C41425293
NT1, NT2: NetTie_2; NetTie-2_SMD_0.2mm
Ra1, Ra2: 4K7; R_0603_1608Metric_Pad0.98x0.95mm_HandSolder; LCSC C2907034
Rb1: 430; R_0603_1608Metric_Pad0.98x0.95mm_HandSolder; LCSC C374586
Rb2: 100; R_0603_1608Metric_Pad0.98x0.95mm_HandSolder; LCSC C125923
Rd1: 1K6; R_0603_1608Metric_Pad0.98x0.95mm_HandSolder; LCSC C374557
Rd2: 820; R_0603_1608Metric_Pad0.98x0.95mm_HandSolder; LCSC C218157
Rf1, Rf2: 6K4; R_0603_1608Metric_Pad0.98x0.95mm_HandSolder; LCSC C374580
Rg1, Rg2: 430; R_0603_1608Metric_Pad0.98x0.95mm_HandSolder; LCSC C374586
Ri1, Ri2: 1K5; R_0603_1608Metric_Pad0.98x0.95mm_HandSolder; LCSC C4022618
Rn1: 10K; R_0603_1608Metric_Pad0.98x0.95mm_HandSolder; LCSC C2906982
Rs1: 60m; R_1206_3216Metric_Pad1.30x1.75mm_HandSolder; LCSC C49164944
Rv1, Rv3, Rv5: 6K4; R_0603_1608Metric_Pad0.98x0.95mm_HandSolder; LCSC C374580
Rv2, Rv4, Rv6: 1K6; R_0603_1608Metric_Pad0.98x0.95mm_HandSolder; LCSC C374557
TH1: 10K/3950; R_0603_1608Metric_Pad0.98x0.95mm_HandSolder; LCSC C2889049
TP1: GND; TestPoint_Pad_D1.0mm
TP2: OPA; TestPoint_Pad_D1.0mm
TP5: VA; TestPoint_Pad_D1.0mm
TP6: VB; TestPoint_Pad_D1.0mm
TP7: VS; TestPoint_Pad_D1.0mm
TP8: VP1; TestPoint_Pad_D1.0mm
TP9: VP2; TestPoint_Pad_D1.0mm

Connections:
+3V3: J5.1, J6.1, J7.2, J11.2, Rb1.1, Rd1.2, Ri1.2, Ri2.2, Rn1.1; also elsewhere on the board
/MCU/ENCA: J6.3, J11.3; also elsewhere on the board
/MCU/ENCB: J6.4, J11.4; also elsewhere on the board
/MCU/OPA_N: Rf2.2, Rg2.2, Ri2.1; also elsewhere on the board
/MCU/OPA_OUT: Rf2.1, TP2.1 (1_1); also elsewhere on the board
/MCU/OPA_P: Rf1.2, Rg1.2, Ri1.1; also elsewhere on the board
/MCU/VPOS1: Ca1.1, Ra1.1, TP8.1 (1_1); also elsewhere on the board
/MCU/VPOS2_NTC: Ca2.1, JP2.2 (C), Ra2.1, TP9.1 (1_1); also elsewhere on the board
/MCU/VSNA: Cv1.1, Rv1.2, Rv2.1, TP5.1 (1_1); also elsewhere on the board
/MCU/VSNB: Cv2.1, Rv3.2, Rv4.1, TP6.1 (1_1); also elsewhere on the board
/MCU/VSNS: Cv3.1, Rv5.2, Rv6.1, TP7.1 (1_1); also elsewhere on the board
/SENS/ISNS+: NT1.1, Rg1.1
/SENS/ISNS-: NT2.1, Rg2.1
/SENS/POS1: J5.3, Ra1.2
/SENS/POS2: J5.4, Ra2.2
/SENS/VB: Cb1.1, Cb2.1, Cv1.2, Cv2.2, Rb1.2, Rb2.1, Rv2.2, Rv4.2
/SENS/VNTC_EXT: J7.1, J11.5, JP2.1 (A)
/SENS/VNTC_INT: JP2.3 (B), Rn1.2, TH1.1
/SENS/VREF: Cd1.1, Rd1.1, Rd2.2, Rf1.1
GND: Ca1.2, Ca2.2, Cb1.2, Cb2.2, Cd1.2, Cv3.2, J5.2, J6.2, J7.3, J11.1, J11.6, NT2.2, Rb2.2, Rd2.1, Rs1.1, Rv6.2, TH1.2, TP1.1 (1_1); also elsewhere on the board
MOT_A: Rv1.1; also elsewhere on the board
MOT_B: Rv3.1; also elsewhere on the board
PGND: NT1.2, Rs1.2; also elsewhere on the board
VSYS: Rv5.1; also elsewhere on the board

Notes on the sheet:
Terminal and supply sense
Current sense shunt
OPA difference amplifier
NTC temperature
Sensor connectors
Servo pot
Rg, Rf, Ri: thinfilm 0.5% 25ppm, C: C0G
SENSORS SUBSYSTEM
NOTES
R: thinfilm 0.5% 25ppm, C: C0G
The whole sensing chain lives on this sheet: shunt -> OPA -> ADC, plus terminal sense, supply sense, two position channels and the NTC. - Rs1 is the ONLY tie between PGND and GND, so all motor return current has to cross it. Don't add another tie in layout. The full layout rules (PGND island, cap r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
RS: 1% 50ppm
